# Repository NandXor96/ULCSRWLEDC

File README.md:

# ULCSRWLEDC
Ultra Low Cost Sound Reactive WLED Controller

## Features

- Small size
- Cheap components
- ICS-43434 MEMS Microphone (optional)
- MOSFET as "Relay"
- Mini Blade Fuse
- Solder Pads instead of Screw Terminal Blocks

## BOM

| Reference | Value | Comment | Estimated Cost per piece |
|---|---|---|---|
| C1, C6 | 100nF | 0805 MLCC | 0.01€ |
| C2 | 10 - 22uF | 0805 MLCC | 0.10€ |
| C3, C4* | 22uF | 0805 MLCC | 0.10€ |
| C5 | 1uF | 0805 MLCC | 0.05€ |
| C7 | >=300uF | Electrolytic Cap D8.0 P3.5 | 0.15€ |
| D1 | SS14 | Schottky | 0.05€ |
| F1 | 2 - 10A | Mini Blade Fuse | 0.50€ |
| MK1** | ICS43434 | optional MEMS Microphone | 0.95 - 2.90€ |
| Q1 | - | SOIC-8 PMOS according to your needs - f.e. IRF7410 | 0.70 - 1.50€ |
| Q2 | - | SOT-23-3 NMOS according to your needs - f.e. IRLML6244 | 0.05 - 0.50€ |
| R1, R3, R5, R7 | 10k | 0805 Resistor | 0.01€ |
| R4 | 100k | 0805 Resistor | 0.01€ |
| R6 | 300R | 0805 Resistor | 0.01€ |
| R2* | 0.03-1R | optional 0805 Resistor | - |
| SW1 | - | Reset Switch SMD 6x3.5mm - f.e. PTS636 | 0.05 - 0.50€ |
| U1 | AMS1117-3.3 | SOT-223-3 LDO | 0.05 - 0.50€ | 
| U2 | ESP-WROOM-32 | ESP32-Module with antenna | 2.85€ |
| PCB | - | JLCPCB | 1.20€ |
|------|------|------|------|
|  |  |  | 5.12 - 10.89€ |

*If you have problems with the stability of the LDO you have two options:
1. Cut the trace resistance between R2 and try some 0805 resistors from 0.03-1ohm.
2. Choose tantal for C4 and bridge R2

** You can build it without the microphone. Then you don't need C6, R4 and MK1.

## Assembly

To assemble the PCB, I recommend using a hot plate or soldering oven for the upper side, and hand-soldering for the ESP32 on the back.
**Preheat** the PCB before soldering anything by hand and use a **powerful soldering iron**!  
Do NOT use a very small tip!

## Disclaimer

The circuit board provided on this GitHub repository is offered "as is," without any warranties or guarantees of any kind. By accessing and utilizing this circuit board, you acknowledge and agree that you do so at your own risk.

The creator and contributor of this repository, shall not be held responsible or liable for any damages, losses, or injuries that may occur as a result of building and / or using this circuit board. This includes but is not limited to any direct, indirect, consequential, or incidental damages.

Electricity is dangerous. Only attempt this project if you know what you're doing.

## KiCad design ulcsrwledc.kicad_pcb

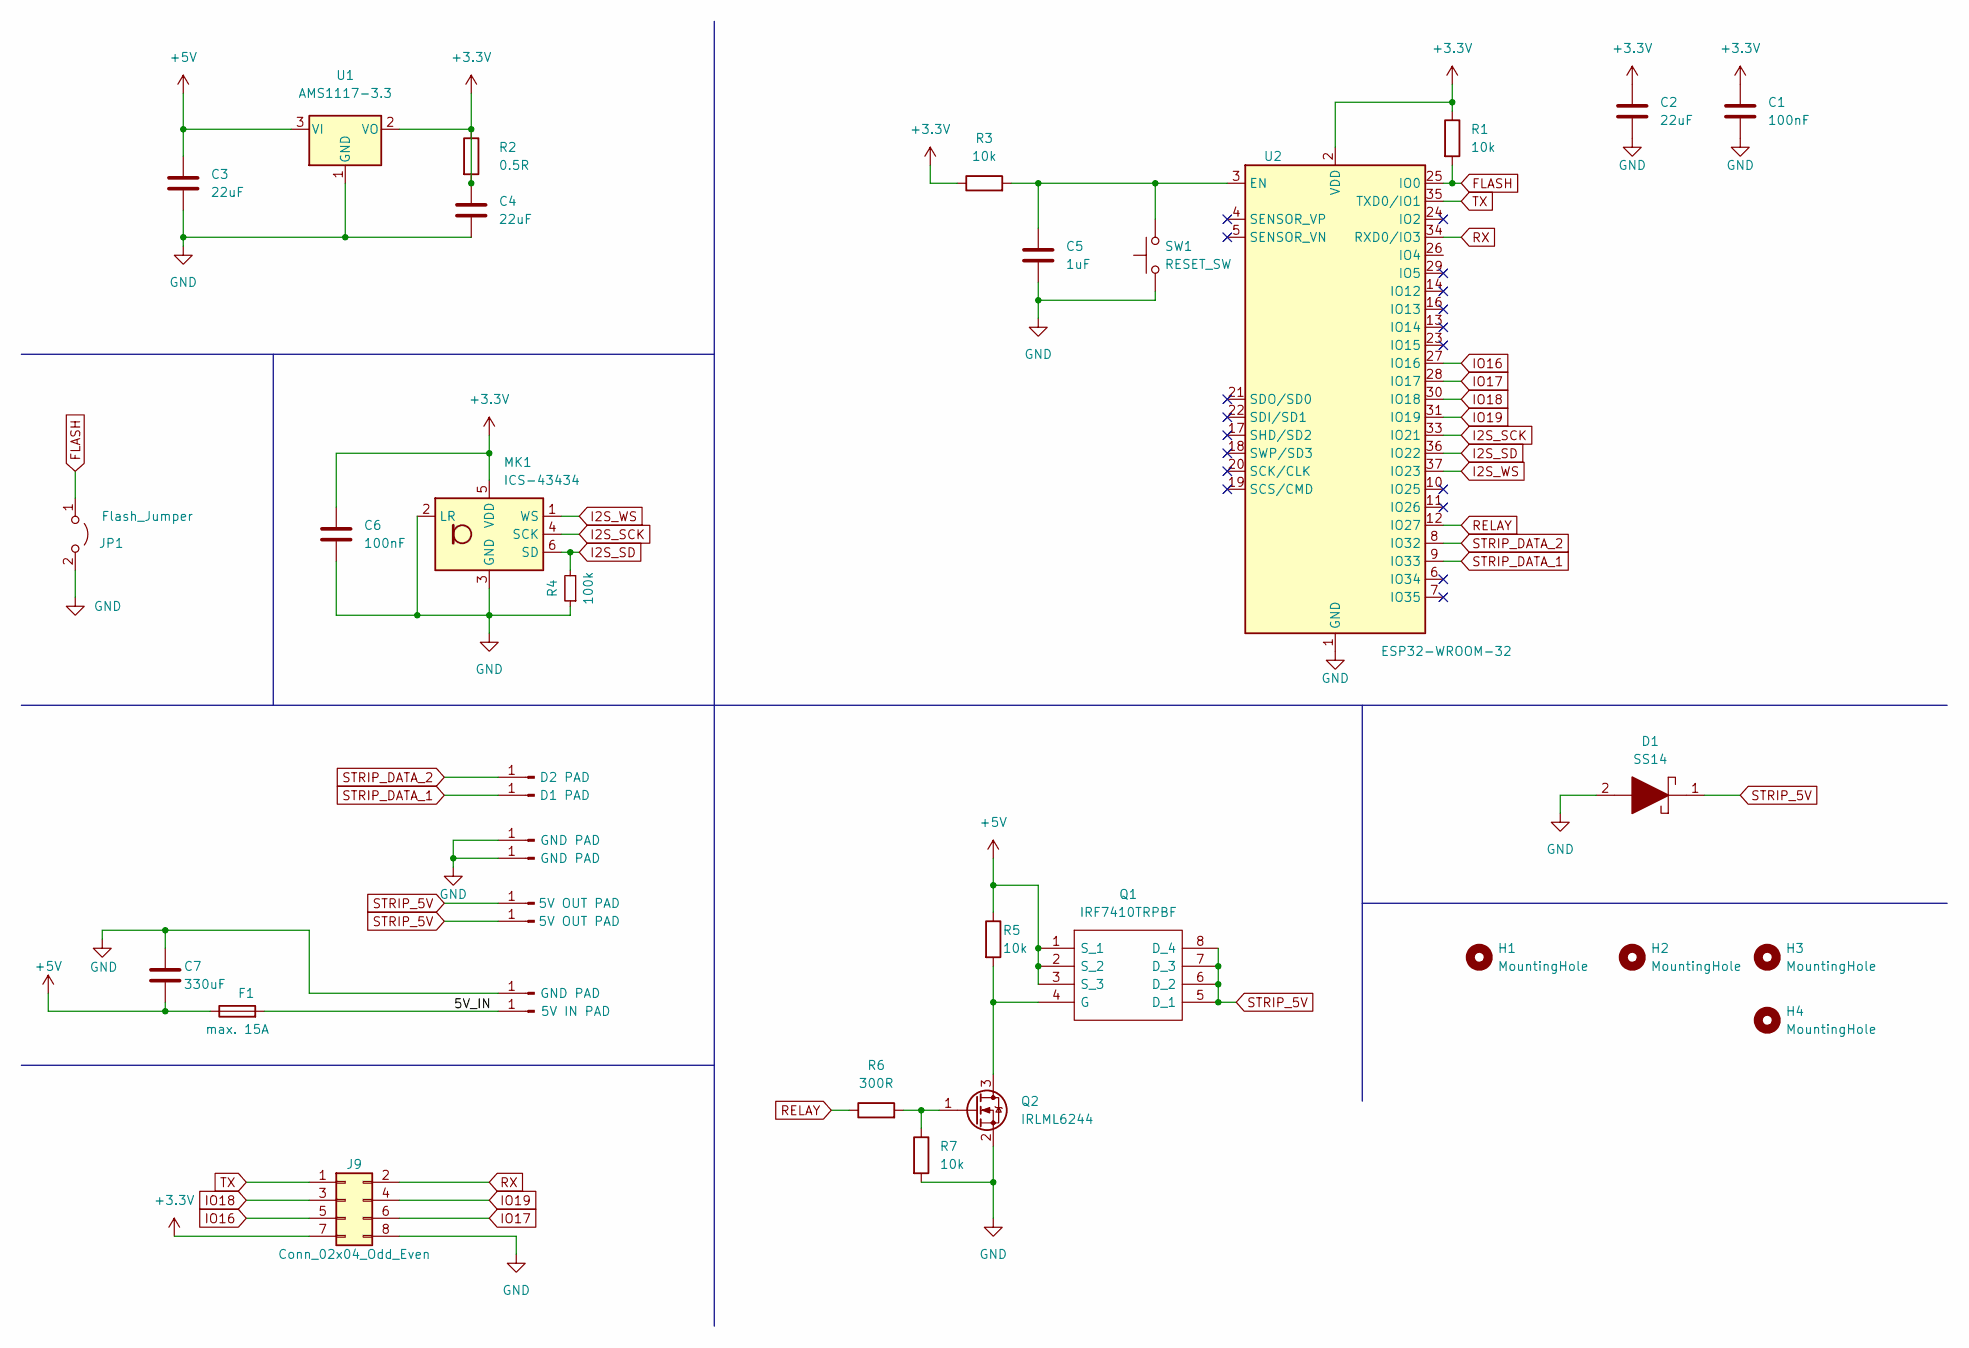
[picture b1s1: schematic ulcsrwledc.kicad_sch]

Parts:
C1, C6: 100nF; C_0805_2012Metric
C2, C3, C4: 22uF; C_0805_2012Metric
C5: 1uF; C_0805_2012Metric
C7: 330uF; CP_Radial_D8.0mm_P3.50mm
D1: SS14; D_SMA
F1: max. 15A; Fuse_Blade_Mini_directSolder
H1, H2, H3, H4: MountingHole; MountingHole_3.2mm_M3_DIN965_Pad_TopBottom
J1, J4: 5V OUT PAD; SolderWirePad_1x01_SMD_3x6mm
J2: D1 PAD; SolderWirePad_1x01_SMD_3x6mm
J3, J6, J7: GND PAD; SolderWirePad_1x01_SMD_3x6mm
J5: D2 PAD; SolderWirePad_1x01_SMD_3x6mm
J8: 5V IN PAD; SolderWirePad_1x01_SMD_3x6mm
J9: Conn_02x04_Odd_Even; PinHeader_2x04_P2.54mm_Vertical
JP1: Flash_Jumper; SolderJumper-2_P1.3mm_Open_RoundedPad1.0x1.5mm
MK1: ICS-43434; InvenSense_ICS-43434-6_3.5x2.65mm
Q1: IRF7410TRPBF; SO-8_3.9x4.9mm_P1.27mm
Q2: IRLML6244; SOT-23-3
R1, R3, R5, R7: 10k; R_0805_2012Metric
R2: 0.5R; R_0805_2012Metric
R4: 100k; R_0805_2012Metric
R6: 300R; R_0805_2012Metric
SW1: RESET_SW; SW_Tactile_SPST_NO_Straight_CK_PTS636Sx25SMTRLFS
U1: AMS1117-3.3; SOT-223-3_TabPin2
U2: ESP32-WROOM-32

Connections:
+3.3V: C1.2, C2.1, C4.1, C6.1, J9.7, MK1.5 (VDD), R1.1, R2.1, R2.2, R3.1, U1.2 (VO), U2.2 (VDD)
+5V: C3.1, C7.1, F1.1, Q1.1 (S_1), Q1.2 (S_2), Q1.3 (S_3), R5.1, U1.3 (VI)
/5V_IN: F1.2, J8.1
FLASH: JP1.1 (A), R1.2, U2.25 (IO0)
GND: C1.1, C2.2, C3.2, C4.2, C5.2, C6.2, C7.2, D1.2, J3.1, J6.1, J7.1, J9.8, JP1.2 (B), MK1.2 (LR), MK1.3 (GND), Q2.2 (S), R4.1, R7.2, SW1.1, U1.1 (GND), U2.1 (GND), U2.15 (GND), U2.38 (GND), U2.39 (GND)
I2S_SCK: MK1.4 (SCK), U2.33 (IO21)
I2S_SD: MK1.6 (SD), R4.2, U2.36 (IO22)
I2S_WS: MK1.1 (WS), U2.37 (IO23)
IO16: J9.5, U2.27 (IO16)
IO17: J9.6, U2.28 (IO17)
IO18: J9.3, U2.30 (IO18)
IO19: J9.4, U2.31 (IO19)
unnamed: Q1.4 (G), Q2.3 (D), R5.2
unnamed: Q2.1 (G), R6.2, R7.1
unnamed: C5.1, R3.2, SW1.2, U2.3 (EN)
RELAY: R6.1, U2.12 (IO27)
RX: J9.2, U2.34 (RXD0/IO3)
STRIP_5V: D1.1, J1.1, J4.1, Q1.5 (D_1), Q1.6 (D_2), Q1.7 (D_3), Q1.8 (D_4)
STRIP_DATA_1: J2.1, U2.9 (IO33)
STRIP_DATA_2: J5.1, U2.8 (IO32)
TX: J9.1, U2.35 (TXD0/IO1)

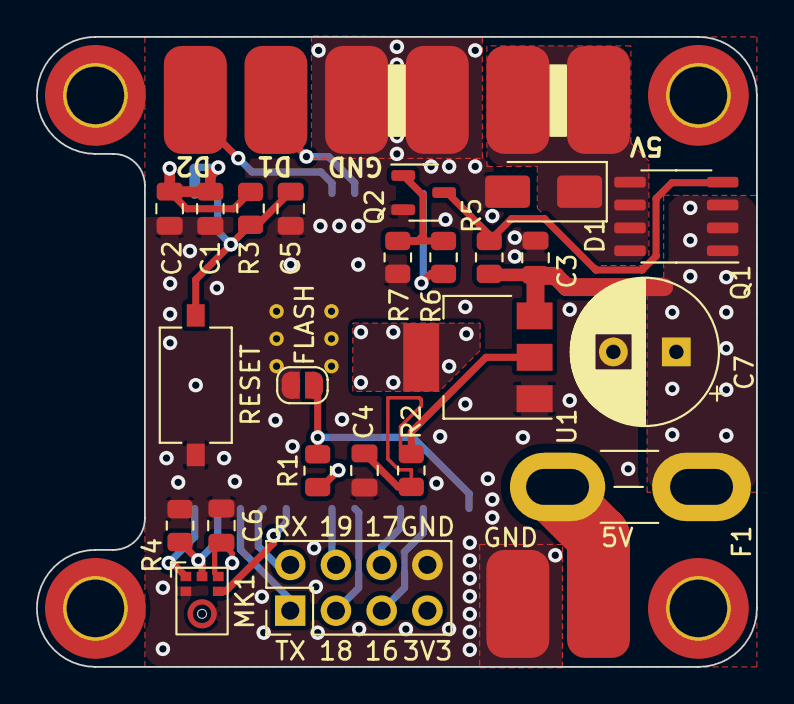
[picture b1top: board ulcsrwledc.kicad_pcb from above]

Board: 4 copper layers, 40.0 x 35.0 mm, 36 parts (1 on the bottom side), 21 nets.

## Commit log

2023-08-08 Update README.md
    Fixed Errors
